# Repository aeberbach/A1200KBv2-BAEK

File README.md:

# A1200KBv2-BAEK</br>

What's a BAEK? It's a Big-Ass Enter Key.</br>

This is the BAEK version of the A1200KBv2 project. It is the same but for the BAEK itself and longer Left Shift key, just like the North American A2000 keyboard. These keys remove the need for two keys that are found in most A1200 keyboards, those that are blank in UK/US languages and are sometimes used for special characters in other languages.</br>
The Left Shift key is a conventionally stabilised key, same as the Right Shift. The BAEK uses the same kind of stabiliser at its base but adds another single stabiliser at the top. The key available does not provide for a vertical wire as keyboards with BAEK sometimes used - when pressing at the very top it will be slightly stiffer, but it seems to work fine.</br>
All other parts of this keyboard are substantially the same as the A1200KBv2 project.</br>

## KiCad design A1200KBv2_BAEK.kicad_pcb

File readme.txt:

What's a BAEK? It's a Big-Ass Enter Key. This is the BAEK version of the A1200KBv2 project. It is the same but for the BAEK itself and longer Left Shift key. These keys remove the need for two keys that are found in most A1200 keyboards, those that are blank in UK/US languages and are sometimes used for special characters in other languages. 
The Left Shift key is a conventionally stabilised key, same as the Right Shift. The BAEK uses the same kind of stabiliser at its base but adds another single stabiliser at the top. The key available does not provide for a vertical wire as keyboard with BAEK sometimes use - when pressing at the very top it will be slightly stiffer, but it seems to work fine.
All other parts of this keyboard are substantially the same as the A1200KBv2 project.

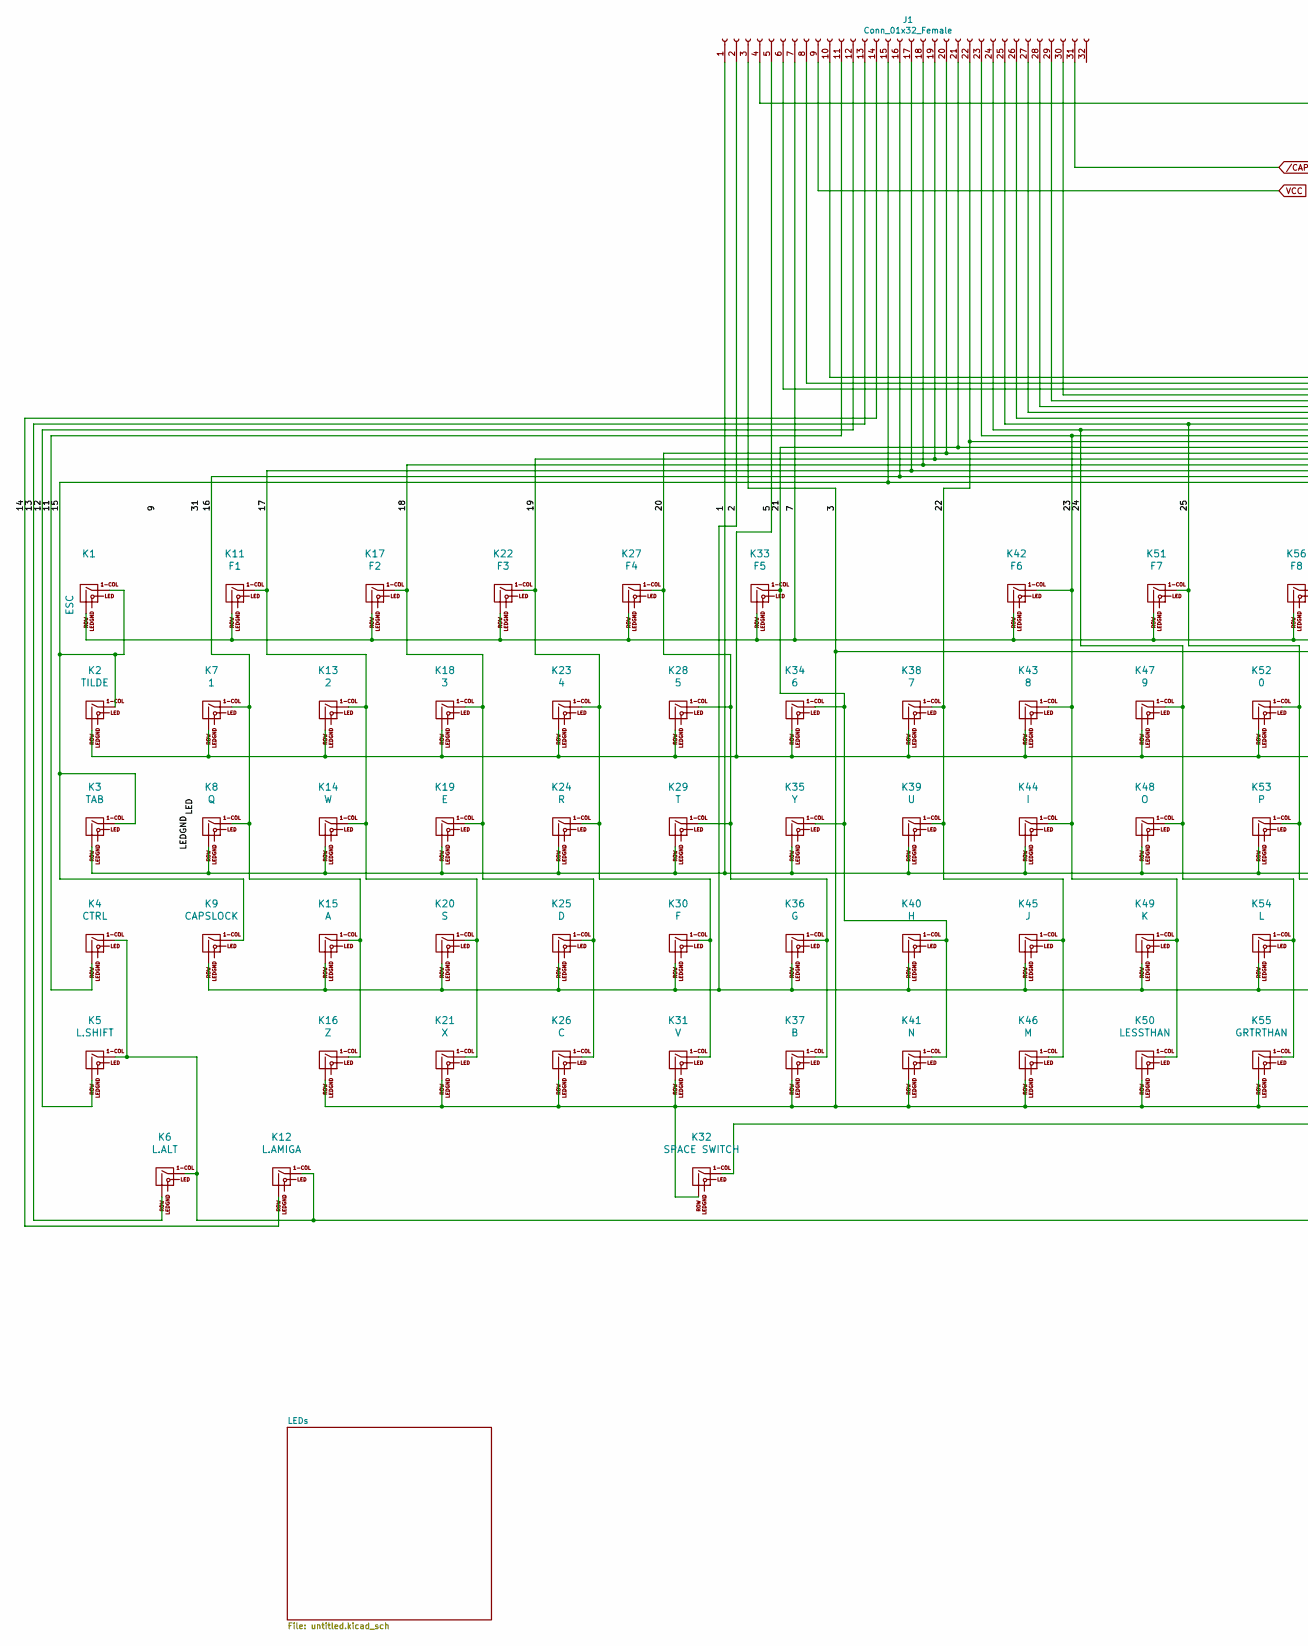
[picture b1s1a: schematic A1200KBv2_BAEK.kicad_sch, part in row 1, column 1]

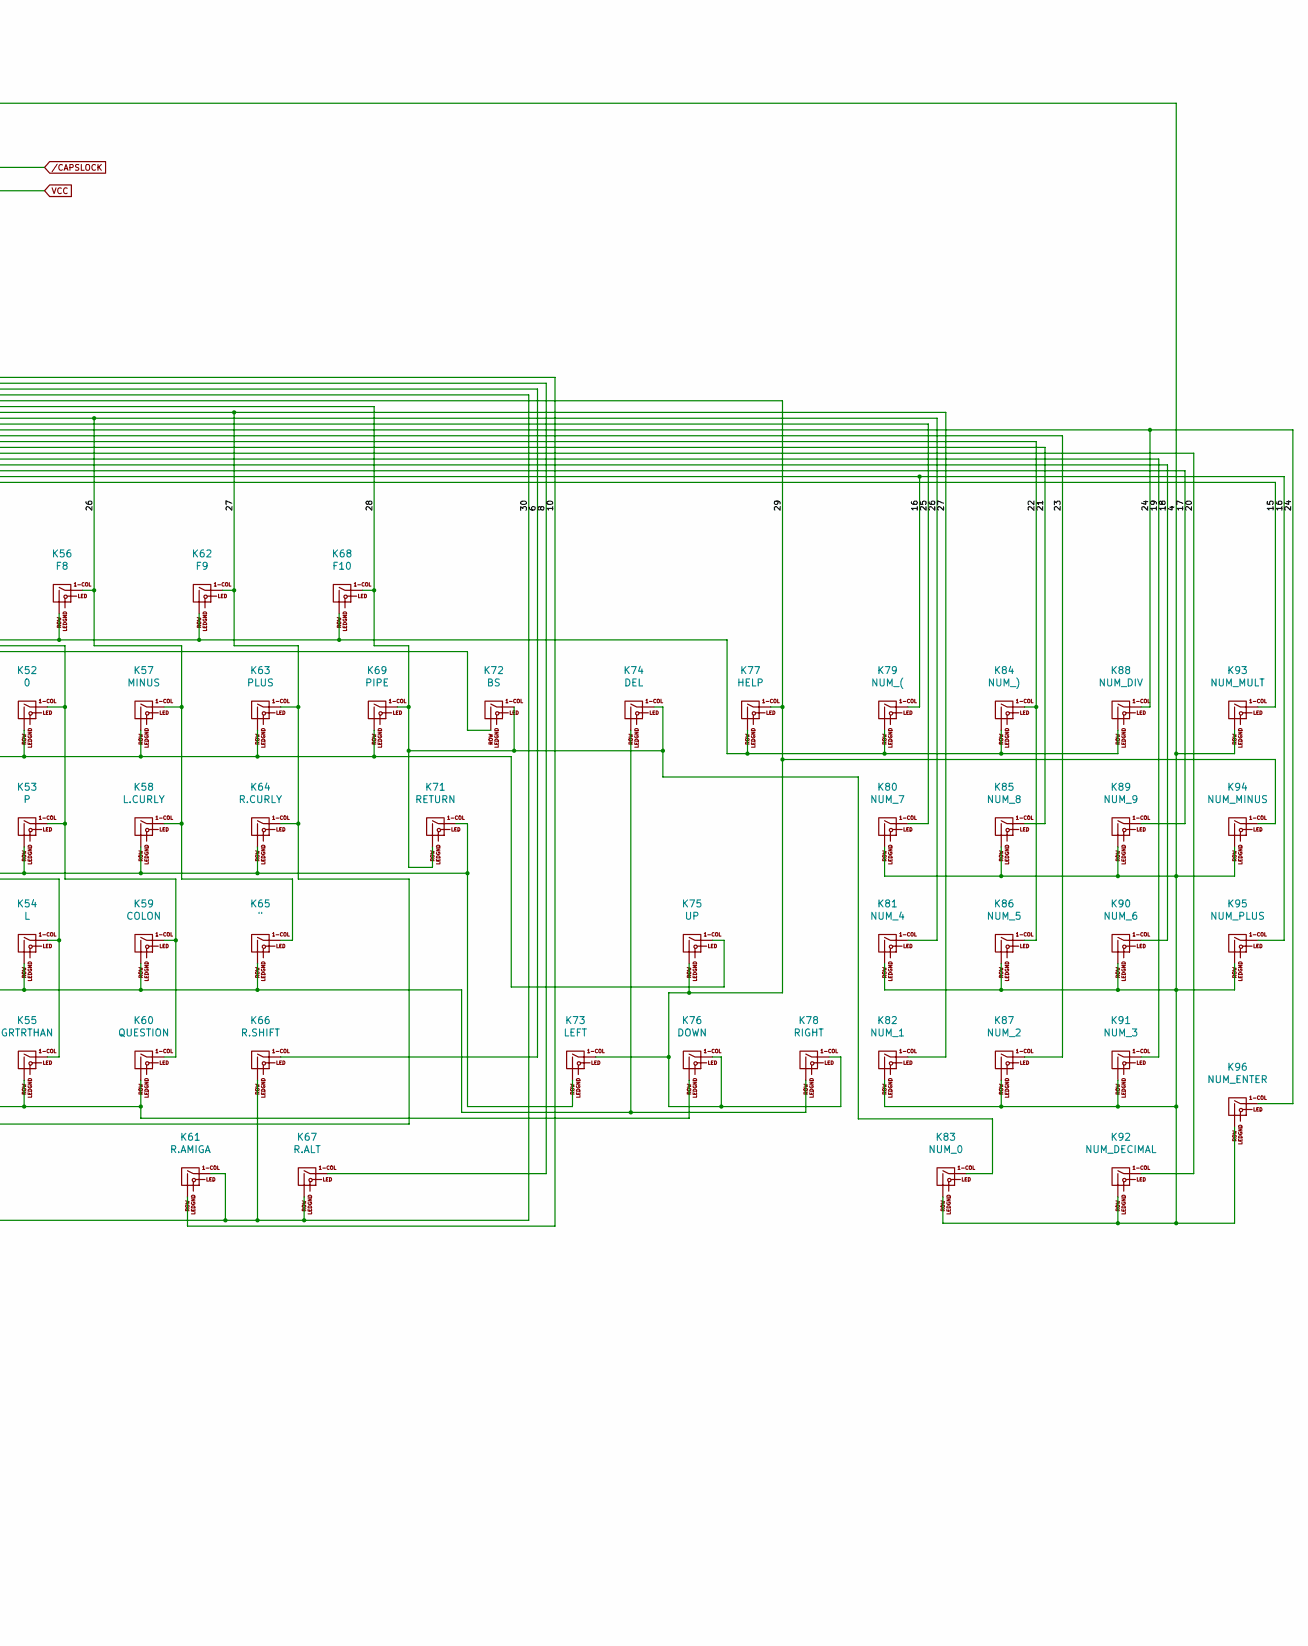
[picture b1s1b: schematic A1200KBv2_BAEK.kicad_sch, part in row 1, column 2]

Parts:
J1: Conn_01x32_Female; FFC-1.25mm-RA-5204403245
K1: ESC; Gateron-KS33-Solderable-1U
K2: TILDE; Gateron-KS33-Solderable-1.5U
K3: TAB; KS-33-2U-stabilizer
K4: CTRL; Gateron-KS33-Solderable-1.25U
K5: L.SHIFT; KS-33-2.75U-stabilizer
K6: L.ALT; Gateron-KS33-Solderable-1.25U
K7: 1; Gateron-KS33-Solderable-1U
K8: Q; Gateron-KS33-Solderable-1U
K9: CAPSLOCK; Gateron-KS33-Solderable-1U
K11: F1; Gateron-KS33-Solderable-1.25U
K12: L.AMIGA; Gateron-KS33-Solderable-1.25U
K13: 2; Gateron-KS33-Solderable-1U
K14: W; Gateron-KS33-Solderable-1U
K15: A; Gateron-KS33-Solderable-1U
K16: Z; Gateron-KS33-Solderable-1U
K17: F2; Gateron-KS33-Solderable-1.25U
K18: 3; Gateron-KS33-Solderable-1U
K19: E; Gateron-KS33-Solderable-1U
K20: S; Gateron-KS33-Solderable-1U
K21: X; Gateron-KS33-Solderable-1U
K22: F3; Gateron-KS33-Solderable-1.25U
K23: 4; Gateron-KS33-Solderable-1U
K24: R; Gateron-KS33-Solderable-1U
K25: D; Gateron-KS33-Solderable-1U
K26: C; Gateron-KS33-Solderable-1U
K27: F4; Gateron-KS33-Solderable-1.25U
K28: 5; Gateron-KS33-Solderable-1U
K29: T; Gateron-KS33-Solderable-1U
K30: F; Gateron-KS33-Solderable-1U
K31: V; Gateron-KS33-Solderable-1U
K32: SPACE SWITCH; KS-33-8U-space
K33: F5; Gateron-KS33-Solderable-1.25U
K34: 6; Gateron-KS33-Solderable-1U
K35: Y; Gateron-KS33-Solderable-1U
K36: G; Gateron-KS33-Solderable-1U
K37: B; Gateron-KS33-Solderable-1U
K38: 7; Gateron-KS33-Solderable-1U
K39: U; Gateron-KS33-Solderable-1U
K40: H; Gateron-KS33-Solderable-1U
K41: N; Gateron-KS33-Solderable-1U
K42: F6; Gateron-KS33-Solderable-1.25U
K43: 8; Gateron-KS33-Solderable-1U
K44: I; Gateron-KS33-Solderable-1U
K45: J; Gateron-KS33-Solderable-1U
K46: M; Gateron-KS33-Solderable-1U
K47: 9; Gateron-KS33-Solderable-1U
K48: O; Gateron-KS33-Solderable-1U
K49: K; Gateron-KS33-Solderable-1U
K50: LESSTHAN; Gateron-KS33-Solderable-1U
K51: F7; Gateron-KS33-Solderable-1.25U
K52: 0; Gateron-KS33-Solderable-1U
K53: P; Gateron-KS33-Solderable-1U
K54: L; Gateron-KS33-Solderable-1U
K55: GRTRTHAN; Gateron-KS33-Solderable-1U
K56: F8; Gateron-KS33-Solderable-1.25U
K57: MINUS; Gateron-KS33-Solderable-1U
K58: L.CURLY; Gateron-KS33-Solderable-1U
K59: COLON; Gateron-KS33-Solderable-1U
K60: QUESTION; Gateron-KS33-Solderable-1U
K61: R.AMIGA; Gateron-KS33-Solderable-1.25U
K62: F9; Gateron-KS33-Solderable-1.25U
K63: PLUS; Gateron-KS33-Solderable-1U
K64: R.CURLY; Gateron-KS33-Solderable-1U
K65: "; Gateron-KS33-Solderable-1U
K66: R.SHIFT; KS-33-2U-stabilizer
K67: R.ALT; Gateron-KS33-Solderable-1.25U
K68: F10; Gateron-KS33-Solderable-1.25U
K69: PIPE; Gateron-KS33-Solderable-1U
K71: RETURN; KS-33-ANSI-BAEK-stabilizer
K72: BS; Gateron-KS33-Solderable-1U
K73: LEFT; Gateron-KS33-Solderable-1U
K74: DEL; Gateron-KS33-Solderable-1.5U
K75: UP; Gateron-KS33-Solderable-1U
K76: DOWN; Gateron-KS33-Solderable-1U
K77: HELP; Gateron-KS33-Solderable-1.5U
K78: RIGHT; Gateron-KS33-Solderable-1U
K79: NUM_(; Gateron-KS33-Solderable-1U
K80: NUM_7; Gateron-KS33-Solderable-1U
K81: NUM_4; Gateron-KS33-Solderable-1U
K82: NUM_1; Gateron-KS33-Solderable-1U
K83: NUM_0; KS-33-2U-stabilizer
K84: NUM_); Gateron-KS33-Solderable-1U
K85: NUM_8; Gateron-KS33-Solderable-1U
K86: NUM_5; Gateron-KS33-Solderable-1U
K87: NUM_2; Gateron-KS33-Solderable-1U
K88: NUM_DIV; Gateron-KS33-Solderable-1U
K89: NUM_9; Gateron-KS33-Solderable-1U
K90: NUM_6; Gateron-KS33-Solderable-1U
K91: NUM_3; Gateron-KS33-Solderable-1U
K92: NUM_DECIMAL; Gateron-KS33-Solderable-1U
K93: NUM_MULT; Gateron-KS33-Solderable-1U
K94: NUM_MINUS; Gateron-KS33-Solderable-1U
K95: NUM_PLUS; Gateron-KS33-Solderable-1U
K96: NUM_ENTER; KS-33-2U-stabilizer

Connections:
/1: J1.1, K3.2 (ROW), K8.2 (ROW), K14.2 (ROW), K19.2 (ROW), K24.2 (ROW), K29.2 (ROW), K35.2 (ROW), K39.2 (ROW), K44.2 (ROW), K48.2 (ROW), K53.2 (ROW), K58.2 (ROW), K64.2 (ROW), K71.1 (COL), K73.2 (ROW)
/2: J1.2, K9.2 (ROW), K15.2 (ROW), K20.2 (ROW), K25.2 (ROW), K30.2 (ROW), K36.2 (ROW), K40.2 (ROW), K45.2 (ROW), K49.2 (ROW), K54.2 (ROW), K59.2 (ROW), K65.2 (ROW), K74.2 (ROW), K78.2 (ROW)
/3: J1.3, K16.2 (ROW), K21.2 (ROW), K26.2 (ROW), K31.2 (ROW), K32.2 (ROW), K37.2 (ROW), K41.2 (ROW), K46.2 (ROW), K50.2 (ROW), K55.2 (ROW), K60.2 (ROW), K72.2 (ROW), K76.2 (ROW)
/4: J1.4, K80.2 (ROW), K81.2 (ROW), K82.2 (ROW), K83.2 (ROW), K85.2 (ROW), K86.2 (ROW), K87.2 (ROW), K89.2 (ROW), K90.2 (ROW), K91.2 (ROW), K92.2 (ROW), K93.2 (ROW), K94.2 (ROW), K95.2 (ROW), K96.2 (ROW)
/5: J1.5, K2.2 (ROW), K7.2 (ROW), K13.2 (ROW), K18.2 (ROW), K23.2 (ROW), K28.2 (ROW), K34.2 (ROW), K38.2 (ROW), K43.2 (ROW), K47.2 (ROW), K52.2 (ROW), K57.2 (ROW), K63.2 (ROW), K69.2 (ROW), K75.1 (COL)
/6: J1.6, K66.1 (COL)
/7: J1.7, K1.2 (ROW), K11.2 (ROW), K17.2 (ROW), K22.2 (ROW), K27.2 (ROW), K33.2 (ROW), K42.2 (ROW), K51.2 (ROW), K56.2 (ROW), K62.2 (ROW), K68.2 (ROW), K77.2 (ROW), K79.2 (ROW), K84.2 (ROW), K88.2 (ROW)
/8: J1.8, K67.1 (COL)
/10: J1.10, K61.2 (ROW)
/11: J1.11, K4.2 (ROW)
/12: J1.12, K5.2 (ROW)
/13: J1.13, K6.2 (ROW)
/14: J1.14, K12.2 (ROW)
/15: J1.15, K1.1 (COL), K2.1 (COL), K3.1 (COL), K9.1 (COL), K93.1 (COL)
/16: J1.16, K7.1 (COL), K8.1 (COL), K15.1 (COL), K16.1 (COL), K79.1 (COL), K95.1 (COL)
/17: J1.17, K11.1 (COL), K13.1 (COL), K14.1 (COL), K20.1 (COL), K21.1 (COL), K89.1 (COL)
/18: J1.18, K17.1 (COL), K18.1 (COL), K19.1 (COL), K25.1 (COL), K26.1 (COL), K90.1 (COL)
/19: J1.19, K22.1 (COL), K23.1 (COL), K24.1 (COL), K30.1 (COL), K31.1 (COL), K91.1 (COL)
/20: J1.20, K27.1 (COL), K28.1 (COL), K29.1 (COL), K36.1 (COL), K37.1 (COL), K92.1 (COL)
/21: J1.21, K33.1 (COL), K34.1 (COL), K35.1 (COL), K40.1 (COL), K41.1 (COL), K85.1 (COL)
/22: J1.22, K38.1 (COL), K39.1 (COL), K45.1 (COL), K46.1 (COL), K84.1 (COL), K86.1 (COL)
/23: J1.23, K42.1 (COL), K43.1 (COL), K44.1 (COL), K49.1 (COL), K50.1 (COL), K87.1 (COL)
/24: J1.24, K47.1 (COL), K48.1 (COL), K54.1 (COL), K55.1 (COL), K88.1 (COL), K96.1 (COL)
/25: J1.25, K51.1 (COL), K52.1 (COL), K53.1 (COL), K59.1 (COL), K60.1 (COL), K80.1 (COL)
/26: J1.26, K56.1 (COL), K57.1 (COL), K58.1 (COL), K65.1 (COL), K81.1 (COL)
/27: J1.27, K32.1 (COL), K62.1 (COL), K63.1 (COL), K64.1 (COL), K82.1 (COL)
/28: J1.28, K68.1 (COL), K69.1 (COL), K71.2 (ROW), K72.1 (COL), K74.1 (COL), K83.1 (COL)
/29: J1.29, K73.1 (COL), K75.2 (ROW), K76.1 (COL), K77.1 (COL), K78.1 (COL), K94.1 (COL)
/30: J1.30, K4.1 (COL), K5.1 (COL), K6.1 (COL), K12.1 (COL), K61.1 (COL), K66.2 (ROW), K67.2 (ROW)
VCC: J1.9; also elsewhere on the board
/CAPSLOCK: J1.31; also elsewhere on the board

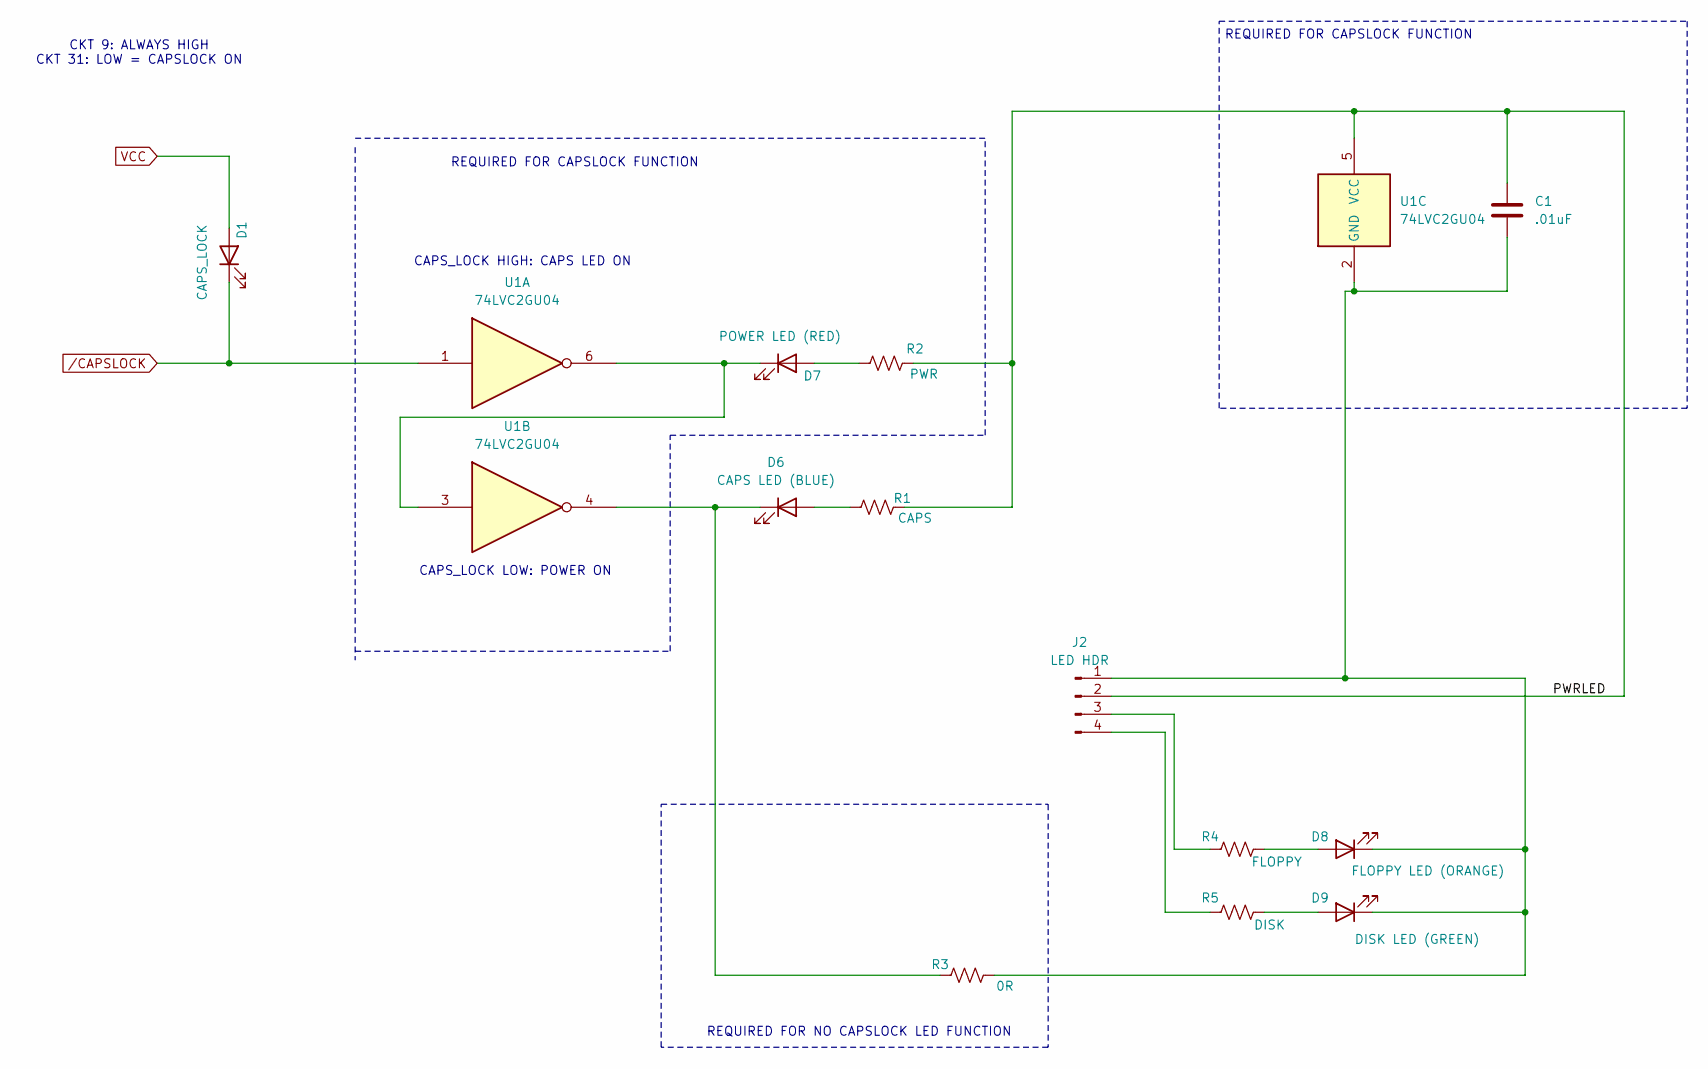
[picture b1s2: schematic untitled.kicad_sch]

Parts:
C1: .01uF; C_0805_2012Metric_Pad1.18x1.45mm_HandSolder
D1: CAPS_LOCK; LED_0805_2012Metric
D6: CAPS LED (BLUE); LED_0805_2012Metric
D7: POWER LED (RED); LED_0805_2012Metric
D8: FLOPPY LED (ORANGE); LED_0805_2012Metric
D9: DISK LED (GREEN); LED_0805_2012Metric
J2: LED HDR; PinHeader_1x04_P2.54mm_Vertical
R1: CAPS; R_0805_2012Metric_Pad1.20x1.40mm_HandSolder
R2: PWR; R_0805_2012Metric_Pad1.20x1.40mm_HandSolder
R3: 0R; R_0805_2012Metric_Pad1.20x1.40mm_HandSolder
R4: FLOPPY; R_0805_2012Metric_Pad1.20x1.40mm_HandSolder
R5: DISK; R_0805_2012Metric_Pad1.20x1.40mm_HandSolder
U1: 74LVC2GU04; SOT-23-6

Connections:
/LEDs/PWRLED: C1.1, J2.2, R1.2, R2.2, U1.5 (VCC)
unnamed: D6.2 (A), R1.1
unnamed: D6.1 (K), R3.1, U1.4
unnamed: D7.2 (A), R2.1
unnamed: D7.1 (K), U1.3, U1.6
unnamed: D8.2 (A), R4.2
unnamed: C1.2, D8.1 (K), D9.1 (K), J2.1, R3.2, U1.2 (GND)
unnamed: D9.2 (A), R5.2
unnamed: J2.3, R4.1
unnamed: J2.4, R5.1
VCC: D1.2 (A); also elsewhere on the board
/CAPSLOCK: D1.1 (K), U1.1; also elsewhere on the board

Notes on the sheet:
CAPS_LOCK LOW: POWER ON
CKT 9: ALWAYS HIGH CKT 31: LOW = CAPSLOCK ON
REQUIRED FOR CAPSLOCK FUNCTION
CAPS_LOCK HIGH: CAPS LED ON
REQUIRED FOR NO CAPSLOCK LED FUNCTION

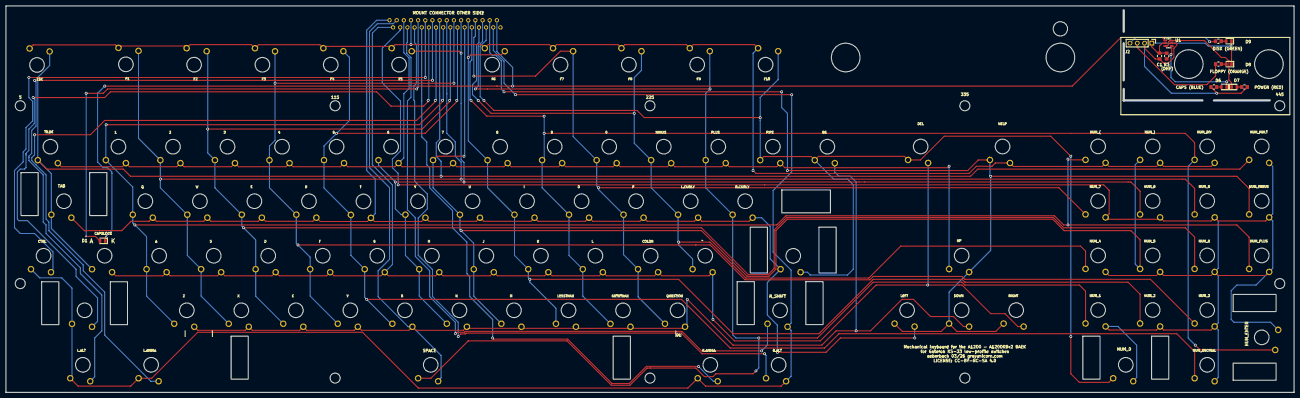
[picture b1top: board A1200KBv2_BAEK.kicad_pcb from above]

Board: 2 copper layers, 450.0 x 135.0 mm, 108 parts (1 on the bottom side), 41 nets.

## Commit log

2026-04-07 Commit of BAEK project
2026-04-07 Readme update
2026-04-07 typo
2026-04-08 STLs for keyboard plates
2026-04-08 Organise 3D print files
2026-06-08 Revised mounts

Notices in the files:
A1200KBv2_BAEK.kicad_pcb:
LICENSE: CC-BY-NC-SA 4.0
